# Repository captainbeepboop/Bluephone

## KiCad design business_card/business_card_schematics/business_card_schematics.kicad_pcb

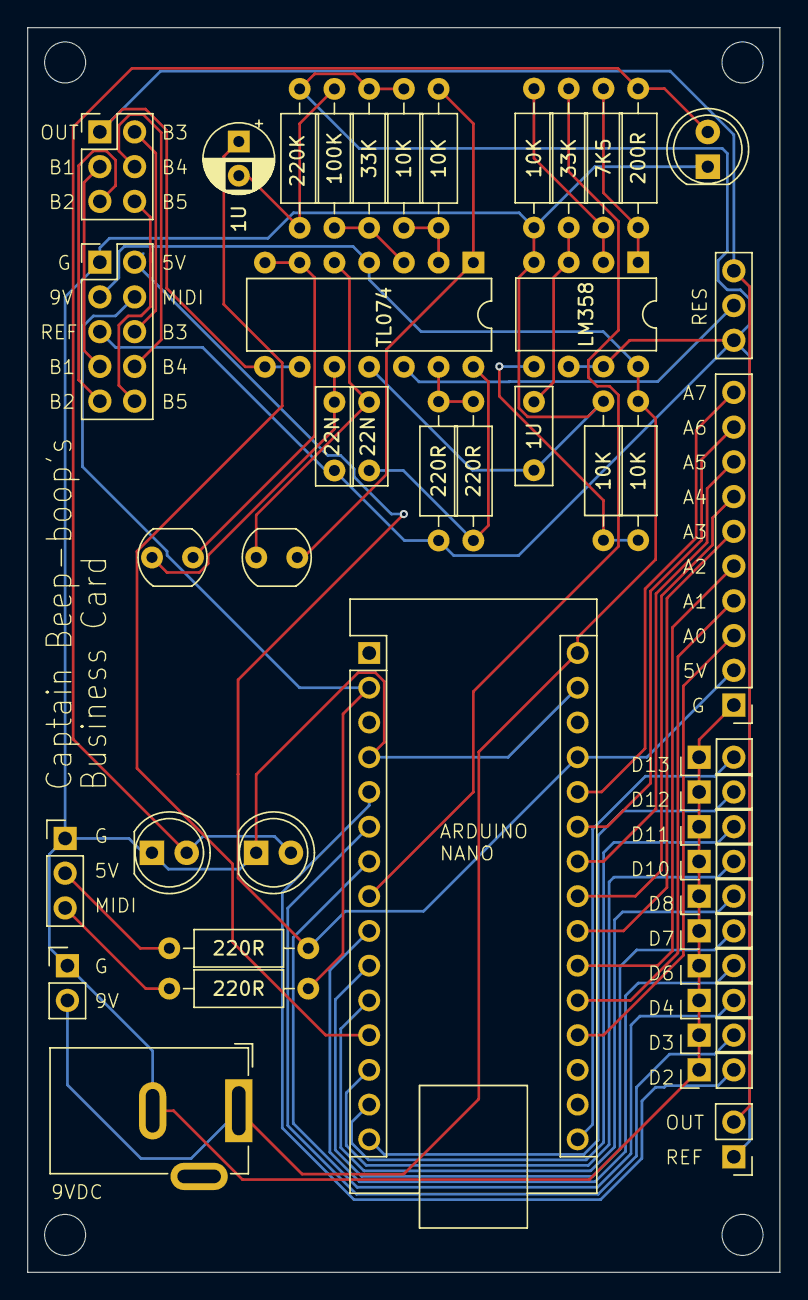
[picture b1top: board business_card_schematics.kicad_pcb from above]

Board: 2 copper layers, 55.0 x 91.0 mm, 45 parts (0 on the bottom side), 48 nets.

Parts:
1U: 1U; C_Disc_D7.0mm_W2.5mm_P5.00mm
1U#2: C_Polarized; CP_Radial_D5.0mm_P2.50mm
7K5, 220R#4: 7K5; R_Axial_DIN0207_L6.3mm_D2.5mm_P10.16mm_Horizontal
10K, 10K#2, 10K#3, 10K#4, 10K#5, 220R#2: 10K; R_Axial_DIN0207_L6.3mm_D2.5mm_P10.16mm_Horizontal
22N, 22N#2: 22N; C_Disc_D7.0mm_W2.5mm_P5.00mm
33K, 33K#2: 33K; R_Axial_DIN0207_L6.3mm_D2.5mm_P10.16mm_Horizontal
100K: 100K; R_Axial_DIN0207_L6.3mm_D2.5mm_P10.16mm_Horizontal
200R, 220R, 220R#3: 220R; R_Axial_DIN0207_L6.3mm_D2.5mm_P10.16mm_Horizontal
220K: 220K; R_Axial_DIN0207_L6.3mm_D2.5mm_P10.16mm_Horizontal
A1: Arduino_Nano_v3.x; Arduino_Nano
D1, D2, D3: LED; LED_D5.0mm
J1: Conn_02x05_Counter_Clockwise; PinHeader_2x05_P2.54mm_Vertical
J2: Conn_02x03_Counter_Clockwise; PinHeader_2x03_P2.54mm_Vertical
J3: Conn_01x03_Pin; PinHeader_1x03_P2.54mm_Vertical
J4: Conn_01x10_Pin; PinHeader_1x10_P2.54mm_Vertical
J5: Barrel_Jack; BarrelJack_GCT_DCJ200-10-A_Horizontal
J6, J7: Conn_01x02_Pin; PinHeader_1x02_P2.54mm_Vertical
LDR1, LDR2: LDR03; R_LDR_5.0x4.1mm_P3mm_Vertical
LM358: LM358; DIP-8_W7.62mm
RV1: R_Potentiometer; PinHeader_1x03_P2.54mm_Vertical
SW1, SW2, SW3, SW4, SW5, SW6, SW7, SW8, SW9, SW10: SW_Push; PinHeader_1x02_P2.54mm_Vertical
TL074: TL074; DIP-14_W7.62mm

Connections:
5V: 220R.2, A1.27 (+5V), J1.2, J4.2
9V: 10K#4.1, A1.30 (VIN), J1.3, J5.1, J6.2, LM358.8 (V+), TL074.4 (V+)
A0: A1.19 (A0), J4.3
A1: A1.20 (A1), J4.4
A2: A1.21 (A2), J4.5
A3: A1.22 (A3), J4.6
A4: A1.23 (A4), J4.7
A5: A1.24 (A5), J4.8
A6: A1.25 (A6), J4.9
A7: A1.26 (A7), J4.10
BUS1: J1.7, J2.3
BUS2: J1.9, J2.5
BUS3: J1.6, J2.2
BUS4: J1.8, J2.4
BUS5: J1.10, J2.6
CV: 33K.1, A1.8 (D5)
D2: A1.5 (D2), SW1.2
D3: A1.6 (D3), SW2.2
D4: A1.7 (D4), SW3.2
D6: A1.9 (D6), SW4.2
D7: A1.10 (D7), SW5.2
D8: A1.11 (D8), SW6.2
D10: A1.13 (D10), SW7.2
D11: A1.14 (D11), SW8.2
D12: A1.15 (D12), SW9.2
D13: A1.16 (D13), SW10.2
GND: 1U.2, 10K.2, 10K#5.2, A1.4 (GND), A1.29 (GND), D1.1 (K), D2.1 (K), D3.1 (K), J1.1, J3.1, J4.1, J5.2, J6.1, LM358.4 (V-), SW1.1, SW2.1, SW3.1, SW4.1, SW5.1, SW6.1, SW7.1, SW8.1, SW9.1, SW10.1, TL074.11 (V-)
MIDI: 220R#3.2, A1.2 (D0/RX), J1.4
unnamed: 1U#2.2, 100K.1, 220K.1
unnamed: 22N.2, 220R#2.1, TL074.14
unnamed: 200R.2, D1.2 (A), D2.2 (A), D3.2 (A)
unnamed: 220R.1, J3.2
unnamed: 220R#3.1, J3.3
unnamed: 10K#2.1, LDR1.2, TL074.1
unnamed: 7K5.1, 200R.1, LM358.1
unnamed: 33K#2.1, 100K.2, TL074.3 (+)
unnamed: 10K#2.2, 10K#3.1, TL074.2 (-)
unnamed: 22N.1, LDR1.1, TL074.5 (+)
unnamed: LDR2.2, TL074.6 (-), TL074.7
unnamed: 22N#2.1, LDR2.1, TL074.10 (+)
unnamed: RV1.2, TL074.12 (+)
unnamed: 220R#2.2, 220R#4.1, TL074.13 (-)
unnamed: 1U.1, 33K.2, LM358.3 (+)
unnamed: 7K5.2, 10K#5.1, LM358.2 (-)
unnamed: 10K.1, 10K#4.2, LM358.5 (+)
OUT: J2.1, J7.2, RV1.3, TL074.8, TL074.9 (-)
Osc: 1U#2.1, A1.12 (D9)
REF: 10K#3.2, 22N#2.2, 33K#2.2, 220K.2, 220R#4.2, J1.5, J7.1, LM358.6 (-), LM358.7, RV1.1

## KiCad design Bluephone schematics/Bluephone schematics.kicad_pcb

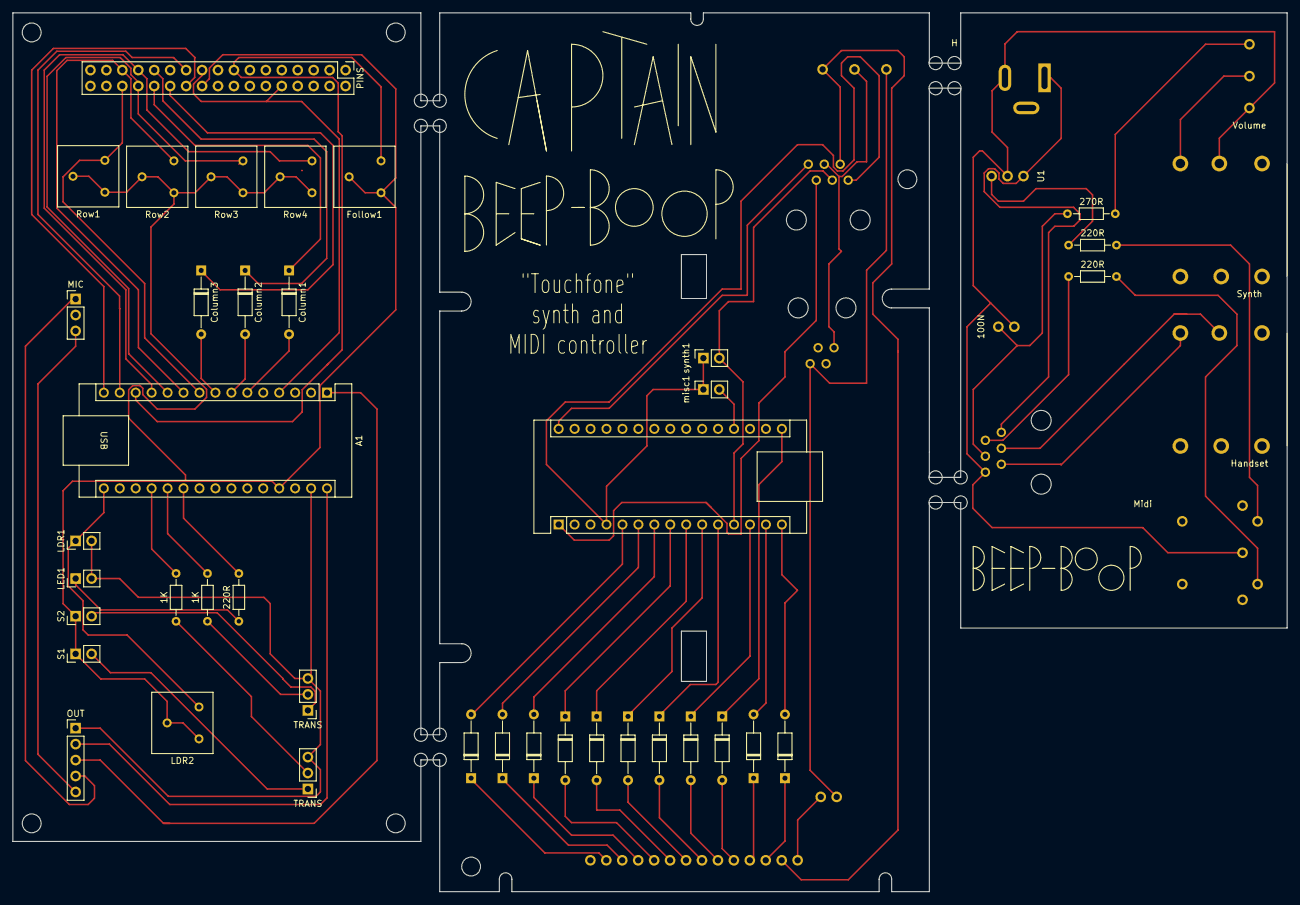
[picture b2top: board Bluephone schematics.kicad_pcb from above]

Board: 2 copper layers, 203.0 x 140.0 mm, 53 parts (0 on the bottom side), 42 nets.

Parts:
1K, 1K#2: 1k; R_Axial_DIN0204_L3.6mm_D1.6mm_P7.62mm_Horizontal
100N: CAP; PinSocket_1x02_P2.54mm_Vertical
220R, 220R#2, 220R#3: 220; R_Axial_DIN0204_L3.6mm_D1.6mm_P7.62mm_Horizontal
270R: R; R_Axial_DIN0204_L3.6mm_D1.6mm_P7.62mm_Horizontal
A1: Arduino_Nano_Every; Arduino_Nano
A1#2: Arduino_Nano_v3.x; Arduino_Nano
Column1, Column2, Column3: DIODE; D_DO-35_SOD27_P10.16mm_Horizontal
D1, D2, D3, D4, D5, D6, D7, D8, D9, D10, D11: DIODE; D_DO-35_SOD27_P10.16mm_Horizontal
Follow1: R; Potentiometer_Bourns_3386F_Vertical
H: HOLE
Handset: AudioJack2; MONO JACK
J1: Conn_01x14_MountingPin; PinSocket_1x14_P2.54mm_Vertical
J2: RJ22; Phone1
J3, J5: RJ14_Shielded; Phone2B
J8: Barrel_Jack; BarrelJack_GCT_DCJ200-10-A_Horizontal
LDR1: Conn_01x02; PinHeader_1x02_P2.54mm_Vertical
LDR2: R; Potentiometer_Bourns_3386F_Vertical
LED1: Conn_01x02; PinHeader_1x02_P2.54mm_Vertical
MIC: Conn_01x03; PinHeader_1x03_P2.54mm_Vertical
Midi: DIN-5; MIDI JACK
OUT: Conn_01x05; PinHeader_1x05_P2.54mm_Vertical
PINS: Conn_02x17_Top_Bottom; 2x17_custom
Row1, Row2, Row3, Row4: R; Potentiometer_Bourns_3386F_Vertical
S1, S2: Conn_01x02; PinHeader_1x02_P2.54mm_Vertical
SW1: SW_Push; MICRO SWITCH
SW2: SW_SPDT; PinSocket_1x02_P2.54mm_Vertical
Synth: AudioJack2; MONO JACK
TRANS: Q_NPN_BCE; PinHeader_1x03_P2.54mm_Vertical
TRANS#2: Q_NPN_BCE; PinHeader_1x03_P2.54mm_Vertical
U1: L7805; PinSocket_1x03_P2.54mm_Vertical
Volume: SW_Push; MICRO SWITCH
misc1: SW_SPDT; PinSocket_1x02_P2.54mm_Vertical
synth1: SW_SPDT; PinSocket_1x02_P2.54mm_Vertical

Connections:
unnamed: 100N.1, 270R.1, J5.2
unnamed: 100N.2, J5.1, J8.2, Midi.3, Synth.2, U1.2 (GND), Volume.3 (C)
unnamed: 220R#2.1, J5.3
unnamed: 220R#2.2, Midi.4
unnamed: 220R.1, U1.3 (OUT)
unnamed: 220R.2, Midi.2
unnamed: 270R.2, Volume.2 (B)
unnamed: A1.1 (D1/TX), A1#2.1 (D1/TX), J3.3, OUT.3
unnamed: A1.4 (GND), A1#2.4 (GND), J3.1, PINS.5, PINS.27, misc1.1, synth1.1
unnamed: A1#2.5 (D2), D1.1 (K)
unnamed: A1.6 (D3), A1#2.6 (D3), Column1.2 (A), D2.1 (K)
unnamed: A1.7 (D4), A1#2.7 (D4), Column2.2 (A), D3.1 (K)
unnamed: A1.8 (D5), A1#2.8 (D5), Column3.2 (A), D4.2 (A)
unnamed: A1.9 (D6), A1#2.9 (D6), D5.2 (A), PINS.15, Row1.1
unnamed: A1.10 (D7), A1#2.10 (D7), D6.2 (A), PINS.32, Row2.1
unnamed: A1.11 (D8), A1#2.11 (D8), D7.2 (A), PINS.14, Row3.1
unnamed: A1.12 (D9), A1#2.12 (D9), J3.2, PINS.31, Row4.1, synth1.2
unnamed: A1.13 (D10), A1#2.13 (D10), D8.2 (A), Follow1.1, PINS.25
unnamed: A1.14 (D11), A1#2.14 (D11), D10.1 (K), PINS.28
unnamed: A1.15 (D12), A1#2.15 (D12), D11.1 (K), PINS.11
unnamed: A1.16 (D13), A1#2.16 (D13), D9.2 (A), LDR1.1, LDR2.1
unnamed: A1.30 (VIN), A1#2.30 (VIN), J3.6, OUT.2
unnamed: D1.2 (A), J1.13
unnamed: D2.2 (A), J1.12
unnamed: D3.2 (A), J1.11
unnamed: D4.1 (K), J1.10
unnamed: D5.1 (K), J1.9
unnamed: D6.1 (K), J1.8
unnamed: D7.1 (K), J1.7
unnamed: D8.1 (K), J1.6
unnamed: D9.1 (K), J1.5
unnamed: D10.2 (A), J1.4
unnamed: D11.2 (A), J1.3
unnamed: Synth.1, Volume.1 (A)
unnamed: J1.1, SW2.1 (A)
unnamed: J1.2, J3.4, SW1.2 (B)
unnamed: J2.2, SW1.3 (C), SW2.2 (B)
unnamed: J2.3, J3.5, MIC.3, OUT.5, SW1.1 (A)
unnamed: Handset.1, J5.4
unnamed: Handset.2, J5.5
unnamed: J5.6, J8.1, U1.1 (IN)
unnamed: A1#2.19 (A0), misc1.2

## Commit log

2023-05-21 First upload to Github. All working.
2023-05-22 Changed the order of the drum preset cycle buttons.
2023-06-07 New updates. Sample drums.
2023-06-07 Some changes.
2024-10-02 21/10/24
2026-03-13 14/03/26
